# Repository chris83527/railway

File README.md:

# railway
Schematics for railway controller

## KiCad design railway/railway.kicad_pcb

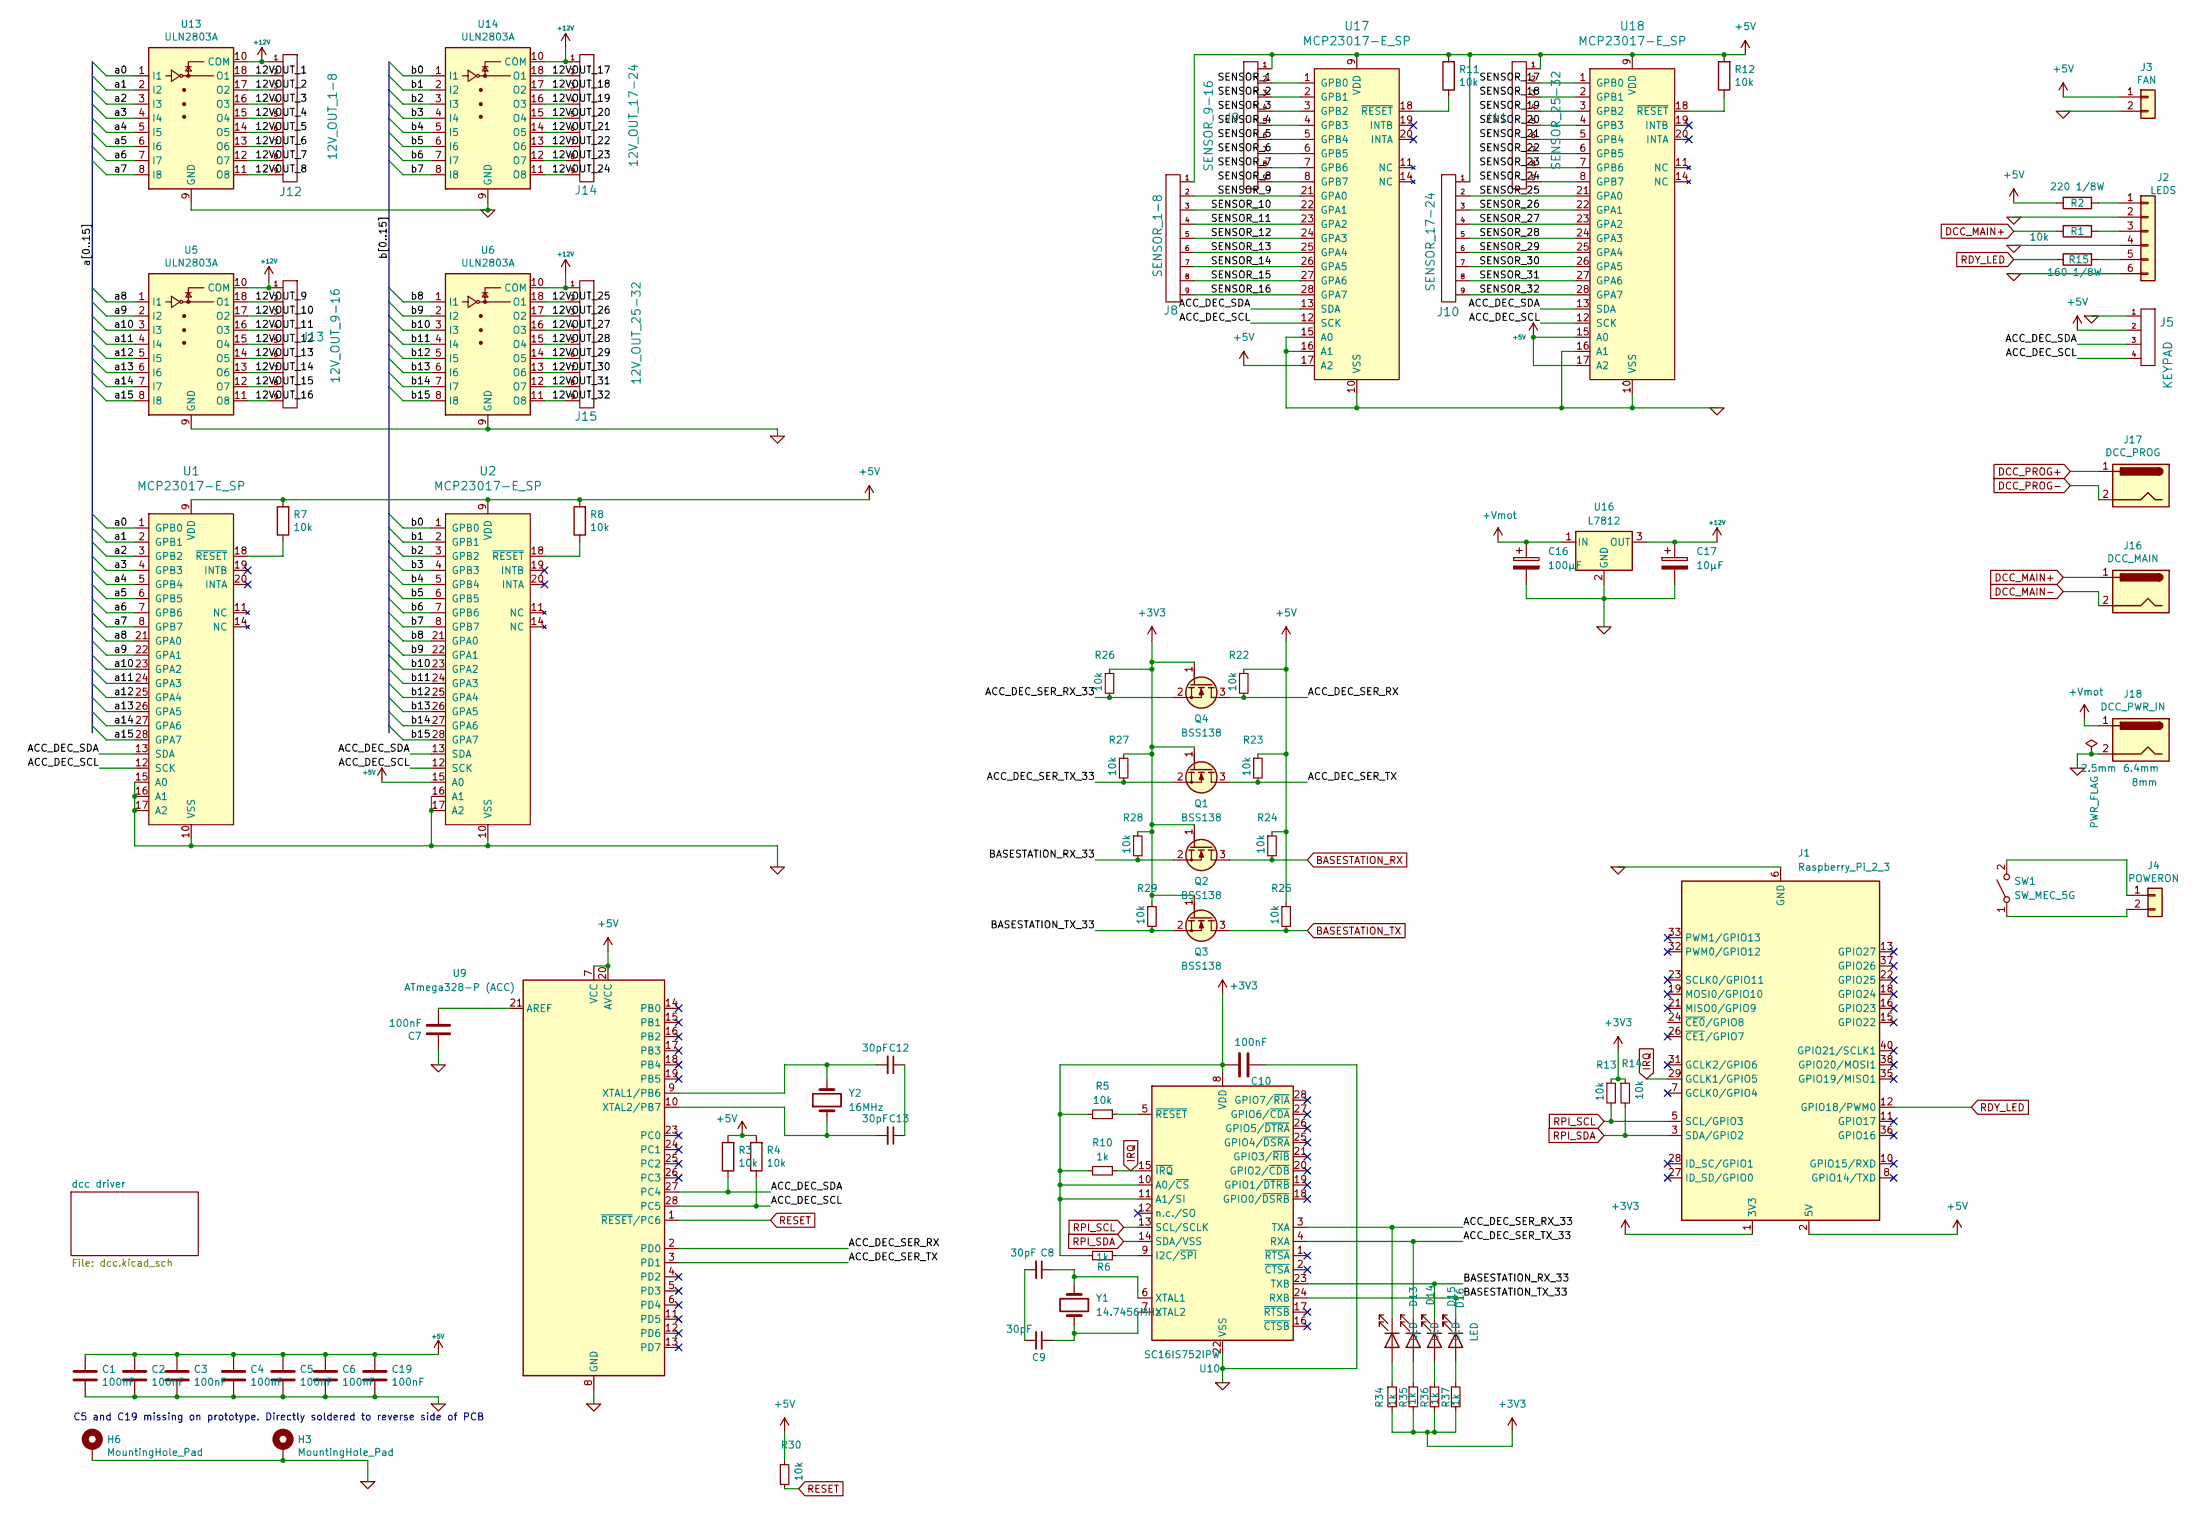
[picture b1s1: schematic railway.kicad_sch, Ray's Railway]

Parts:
C1, C2, C3, C4, C5, C6, C7, C10, C19: 100nF; C_0805_2012Metric_Pad1.18x1.45mm_HandSolder
C8, C9, C12, C13: 30pF; C_0805_2012Metric_Pad1.18x1.45mm_HandSolder
C16: 100µF; CP_Elec_4x4.5
C17: 10µF; CP_Elec_8x10.5
D13, D14, D15, D16: LED; LED_0805_2012Metric_Pad1.15x1.40mm_HandSolder
H3, H6: MountingHole_Pad; MountingHole_3.2mm_M3_Pad
J1: Raspberry_Pi_2_3; IDC-Header_2x20_P2.54mm_Vertical_reversed
J2: LEDS; JST_XH_B6B-XH-A_1x06_P2.50mm_Vertical
J3: FAN; JST_XH_B2B-XH-A_1x02_P2.50mm_Vertical
J4: POWERON; JST_XH_B2B-XH-A_1x02_P2.50mm_Vertical
J5: KEYPAD; JST_XH_B4B-XH-A_1x04_P2.50mm_Vertical
J8: SENSOR_1-8; minidin_9_pcb_mount
J9: SENSOR_9-16; minidin_9_pcb_mount
J10: SENSOR_17-24; minidin_9_pcb_mount
J11: SENSOR_25-32; minidin_9_pcb_mount
J12: 12V_OUT_1-8; minidin_9_pcb_mount
J13: 12V_OUT_9-16; minidin_9_pcb_mount
J14: 12V_OUT_17-24; minidin_9_pcb_mount
J15: 12V_OUT_25-32; minidin_9_pcb_mount
J16: DCC_MAIN; BarrelJack_Wuerth_6941xx301002
J17: DCC_PROG; BarrelJack_Wuerth_6941xx301002
J18: DCC_PWR_IN; BarrelJack_Wuerth_6941xx301002
Q1, Q2, Q3, Q4: BSS138; SOT-23
R1, R5, R7, R8, R11, R12, R13, R14, R22, R23, R24, R25, R26, R27, R28, R29, R30: 10k; R_0805_2012Metric_Pad1.20x1.40mm_HandSolder
R2: 220 1/8W; R_0805_2012Metric_Pad1.20x1.40mm_HandSolder
R3, R4: 10k; R_0805_2012Metric
R6, R10, R34, R35, R36, R37: 1k; R_0805_2012Metric_Pad1.20x1.40mm_HandSolder
R15: 160 1/8W; R_0805_2012Metric_Pad1.20x1.40mm_HandSolder
SW1: SW_MEC_5G; SW_Tactile_SKHH_Angled
U1, U2, U17, U18: MCP23017-E_SP; DIP-28_W7.62mm_Socket_LongPads; MPN MCP23017-E/SP; Digi-Key_PN MCP23017-E/SP-ND
U5, U6, U13, U14: ULN2803A; DIP-18_W7.62mm_Socket
U9: ATmega328-P (ACC); DIP-28_W7.62mm_Socket_LongPads
U10: SC16IS752IPW; TSSOP-28_4.4x9.7mm_P0.65mm
U16: L7812; TO-263-2
Y1: 14.7456MHz; Crystal_SMD_HC49-SD
Y2: 16MHz; Crystal_SMD_ECS_CSM3X-2Pin_7.6x4.1mm

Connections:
+3V3: C10.2, J1.1 (3V3), J1.17 (3V3), Q1.1 (G), Q2.1 (G), Q3.1 (G), Q4.1 (G), R5.2, R6.2, R10.2, R13.1, R14.1, R26.1, R27.1, R28.1, R29.1, R34.2, R35.2, R36.2, R37.2, U10.8 (VDD), U10.10 (A0/~CS), U10.11 (A1/SI)
+5V: C1.1, C2.1, C3.1, C4.1, C5.1, C6.1, C19.1, J1.2 (5V), J1.4 (5V), J3.1, J5.2, J8.1, J9.1, J10.1, J11.1, R2.1, R3.2, R4.2, R7.2, R8.2, R11.2, R12.2, R22.1, R23.1, R24.1, R25.1, R30.1, U1.9 (VDD), U2.9 (VDD), U2.15 (A0), U9.7 (VCC), U9.20 (AVCC), U17.9 (VDD), U17.17 (A2), U18.9 (VDD), U18.15 (A0), U18.17 (A2); also elsewhere on the board
+12V: C17.1, J12.1, J13.1, J14.1, J15.1, U5.10 (COM), U6.10 (COM), U13.10 (COM), U14.10 (COM), U16.3 (OUT)
+Vmot: C16.1, J18.1, U16.1 (IN); also elsewhere on the board
/12VOUT_1: J12.2, U13.18 (O1)
/12VOUT_2: J12.3, U13.17 (O2)
/12VOUT_3: J12.4, U13.16 (O3)
/12VOUT_4: J12.5, U13.15 (O4)
/12VOUT_5: J12.6, U13.14 (O5)
/12VOUT_6: J12.7, U13.13 (O6)
/12VOUT_7: J12.8, U13.12 (O7)
/12VOUT_8: J12.9, U13.11 (O8)
/12VOUT_9: J13.2, U5.18 (O1)
/12VOUT_10: J13.3, U5.17 (O2)
/12VOUT_11: J13.4, U5.16 (O3)
/12VOUT_12: J13.5, U5.15 (O4)
/12VOUT_13: J13.6, U5.14 (O5)
/12VOUT_14: J13.7, U5.13 (O6)
/12VOUT_15: J13.8, U5.12 (O7)
/12VOUT_16: J13.9, U5.11 (O8)
/12VOUT_17: J14.2, U14.18 (O1)
/12VOUT_18: J14.3, U14.17 (O2)
/12VOUT_19: J14.4, U14.16 (O3)
/12VOUT_20: J14.5, U14.15 (O4)
/12VOUT_21: J14.6, U14.14 (O5)
/12VOUT_22: J14.7, U14.13 (O6)
/12VOUT_23: J14.8, U14.12 (O7)
/12VOUT_24: J14.9, U14.11 (O8)
/12VOUT_25: J15.2, U6.18 (O1)
/12VOUT_26: J15.3, U6.17 (O2)
/12VOUT_27: J15.4, U6.16 (O3)
/12VOUT_28: J15.5, U6.15 (O4)
/12VOUT_29: J15.6, U6.14 (O5)
/12VOUT_30: J15.7, U6.13 (O6)
/12VOUT_31: J15.8, U6.12 (O7)
/12VOUT_32: J15.9, U6.11 (O8)
/ACC_DEC_SCL: J5.4, R4.1, U1.12 (SCK), U2.12 (SCK), U9.28 (PC5), U17.12 (SCK), U18.12 (SCK)
/ACC_DEC_SDA: J5.3, R3.1, U1.13 (SDA), U2.13 (SDA), U9.27 (PC4), U17.13 (SDA), U18.13 (SDA)
/ACC_DEC_SER_RX: Q4.3 (D), R22.2, U9.2 (PD0)
/ACC_DEC_SER_RX_33: D13.1 (K), Q4.2 (S), R26.2, U10.3 (TXA)
/ACC_DEC_SER_TX: Q1.3 (D), R23.2, U9.3 (PD1)
/ACC_DEC_SER_TX_33: D14.1 (K), Q1.2 (S), R27.2, U10.4 (RXA)
/BASESTATION_RX_33: D15.1 (K), Q2.2 (S), R28.2, U10.23 (TXB)
/BASESTATION_TX_33: D16.1 (K), Q3.2 (S), R29.2, U10.24 (RXB)
/SENSOR_1: J9.2, U17.1 (GPB0)
/SENSOR_2: J9.3, U17.2 (GPB1)
/SENSOR_3: J9.4, U17.3 (GPB2)
/SENSOR_4: J9.5, U17.4 (GPB3)
/SENSOR_5: J9.6, U17.5 (GPB4)
/SENSOR_6: J9.7, U17.6 (GPB5)
/SENSOR_7: J9.8, U17.7 (GPB6)
/SENSOR_8: J9.9, U17.8 (GPB7)
/SENSOR_9: J8.2, U17.21 (GPA0)
/SENSOR_10: J8.3, U17.22 (GPA1)
/SENSOR_11: J8.4, U17.23 (GPA2)
/SENSOR_12: J8.5, U17.24 (GPA3)
/SENSOR_13: J8.6, U17.25 (GPA4)
/SENSOR_14: J8.7, U17.26 (GPA5)
/SENSOR_15: J8.8, U17.27 (GPA6)
/SENSOR_16: J8.9, U17.28 (GPA7)
/SENSOR_17: J11.2, U18.1 (GPB0)
/SENSOR_18: J11.3, U18.2 (GPB1)
/SENSOR_19: J11.4, U18.3 (GPB2)
/SENSOR_20: J11.5, U18.4 (GPB3)
/SENSOR_21: J11.6, U18.5 (GPB4)
/SENSOR_22: J11.7, U18.6 (GPB5)
/SENSOR_23: J11.8, U18.7 (GPB6)
/SENSOR_24: J11.9, U18.8 (GPB7)
/SENSOR_25: J10.2, U18.21 (GPA0)
/SENSOR_26: J10.3, U18.22 (GPA1)
/SENSOR_27: J10.4, U18.23 (GPA2)
/SENSOR_28: J10.5, U18.24 (GPA3)
/SENSOR_29: J10.6, U18.25 (GPA4)
/SENSOR_30: J10.7, U18.26 (GPA5)
/SENSOR_31: J10.8, U18.27 (GPA6)
/SENSOR_32: J10.9, U18.28 (GPA7)
/a0: U1.1 (GPB0), U13.1 (I1)
/a1: U1.2 (GPB1), U13.2 (I2)
/a2: U1.3 (GPB2), U13.3 (I3)
/a3: U1.4 (GPB3), U13.4 (I4)
/a4: U1.5 (GPB4), U13.5 (I5)
/a5: U1.6 (GPB5), U13.6 (I6)
/a6: U1.7 (GPB6), U13.7 (I7)
/a7: U1.8 (GPB7), U13.8 (I8)
/a8: U1.21 (GPA0), U5.1 (I1)
/a9: U1.22 (GPA1), U5.2 (I2)
/a10: U1.23 (GPA2), U5.3 (I3)
/a11: U1.24 (GPA3), U5.4 (I4)
/a12: U1.25 (GPA4), U5.5 (I5)
/a13: U1.26 (GPA5), U5.6 (I6)
/a14: U1.27 (GPA6), U5.7 (I7)
/a15: U1.28 (GPA7), U5.8 (I8)
/b0: U2.1 (GPB0), U14.1 (I1)
/b1: U2.2 (GPB1), U14.2 (I2)
/b2: U2.3 (GPB2), U14.3 (I3)
/b3: U2.4 (GPB3), U14.4 (I4)
/b4: U2.5 (GPB4), U14.5 (I5)
/b5: U2.6 (GPB5), U14.6 (I6)
/b6: U2.7 (GPB6), U14.7 (I7)
/b7: U2.8 (GPB7), U14.8 (I8)
/b8: U2.21 (GPA0), U6.1 (I1)
/b9: U2.22 (GPA1), U6.2 (I2)
/b10: U2.23 (GPA2), U6.3 (I3)
/b11: U2.24 (GPA3), U6.4 (I4)
/b12: U2.25 (GPA4), U6.5 (I5)
/b13: U2.26 (GPA5), U6.6 (I6)
/b14: U2.27 (GPA6), U6.7 (I7)
/b15: U2.28 (GPA7), U6.8 (I8)
BASESTATION_RX: Q2.3 (D), R24.2; also elsewhere on the board
BASESTATION_TX: Q3.3 (D), R25.2; also elsewhere on the board
DCC_MAIN+: J16.1, R1.1; also elsewhere on the board
DCC_MAIN-: J16.2; also elsewhere on the board
DCC_PROG+: J17.1; also elsewhere on the board
DCC_PROG-: J17.2; also elsewhere on the board
GND: C1.2, C2.2, C3.2, C4.2, C5.2, C6.2, C7.1, C10.1, C16.2, C17.2, C19.2, H3.1, H6.1, J1.6 (GND), J1.9 (GND), J1.14 (GND), J1.20 (GND), J1.25 (GND), J1.30 (GND), J1.34 (GND), J1.39 (GND), J2.2, J2.4, J2.6, J3.2, J5.1, J18.2, U1.10 (VSS), U1.15 (A0), U1.16 (A1), U1.17 (A2), U2.10 (VSS), U2.16 (A1), U2.17 (A2), U5.9 (GND), U6.9 (GND), U9.8 (GND), U9.22 (GND), U10.22 (VSS), U13.9 (GND), U14.9 (GND), U16.2 (GND), U17.10 (VSS), U17.15 (A0), U17.16 (A1), U18.10 (VSS), U18.16 (A1); also elsewhere on the board
IRQ: J1.29 (GCLK1/GPIO5), R10.1, U10.15 (~IRQ)
unnamed: C8.2, C9.2
unnamed: C12.1, C13.1
unnamed: D13.2 (A), R34.1
unnamed: D14.2 (A), R35.1
unnamed: D15.2 (A), R36.1
unnamed: D16.2 (A), R37.1
unnamed: J2.1, R2.2
unnamed: J2.3, R1.2
unnamed: J2.5, R15.2
unnamed: J4.1, SW1.2 (B)
unnamed: J4.2, SW1.1 (A)
unnamed: R7.1, U1.18 (~RESET)
unnamed: R8.1, U2.18 (~RESET)
unnamed: C7.2, U9.21 (AREF)
unnamed: C12.2, U9.9 (XTAL1/PB6), Y2.2
unnamed: C13.2, U9.10 (XTAL2/PB7), Y2.1
unnamed: R6.1, U10.9 (I2C/~SPI)
unnamed: C8.1, U10.6 (XTAL1), Y1.1
unnamed: C9.1, U10.7 (XTAL2), Y1.2
unnamed: R5.1, U10.5 (~RESET)
unnamed: R11.1, U17.18 (~RESET)
unnamed: R12.1, U18.18 (~RESET)
RDY_LED: J1.12 (GPIO18/PWM0), R15.1
RESET: R30.2, U9.1 (~RESET/PC6); also elsewhere on the board
RPI_SCL: J1.5 (SCL/GPIO3), R13.2, U10.13 (SCL/SCLK)
RPI_SDA: J1.3 (SDA/GPIO2), R14.2, U10.14 (SDA/VSS)

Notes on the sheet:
C5 and C19 missing on prototype. Directly soldered to reverse side of PCB

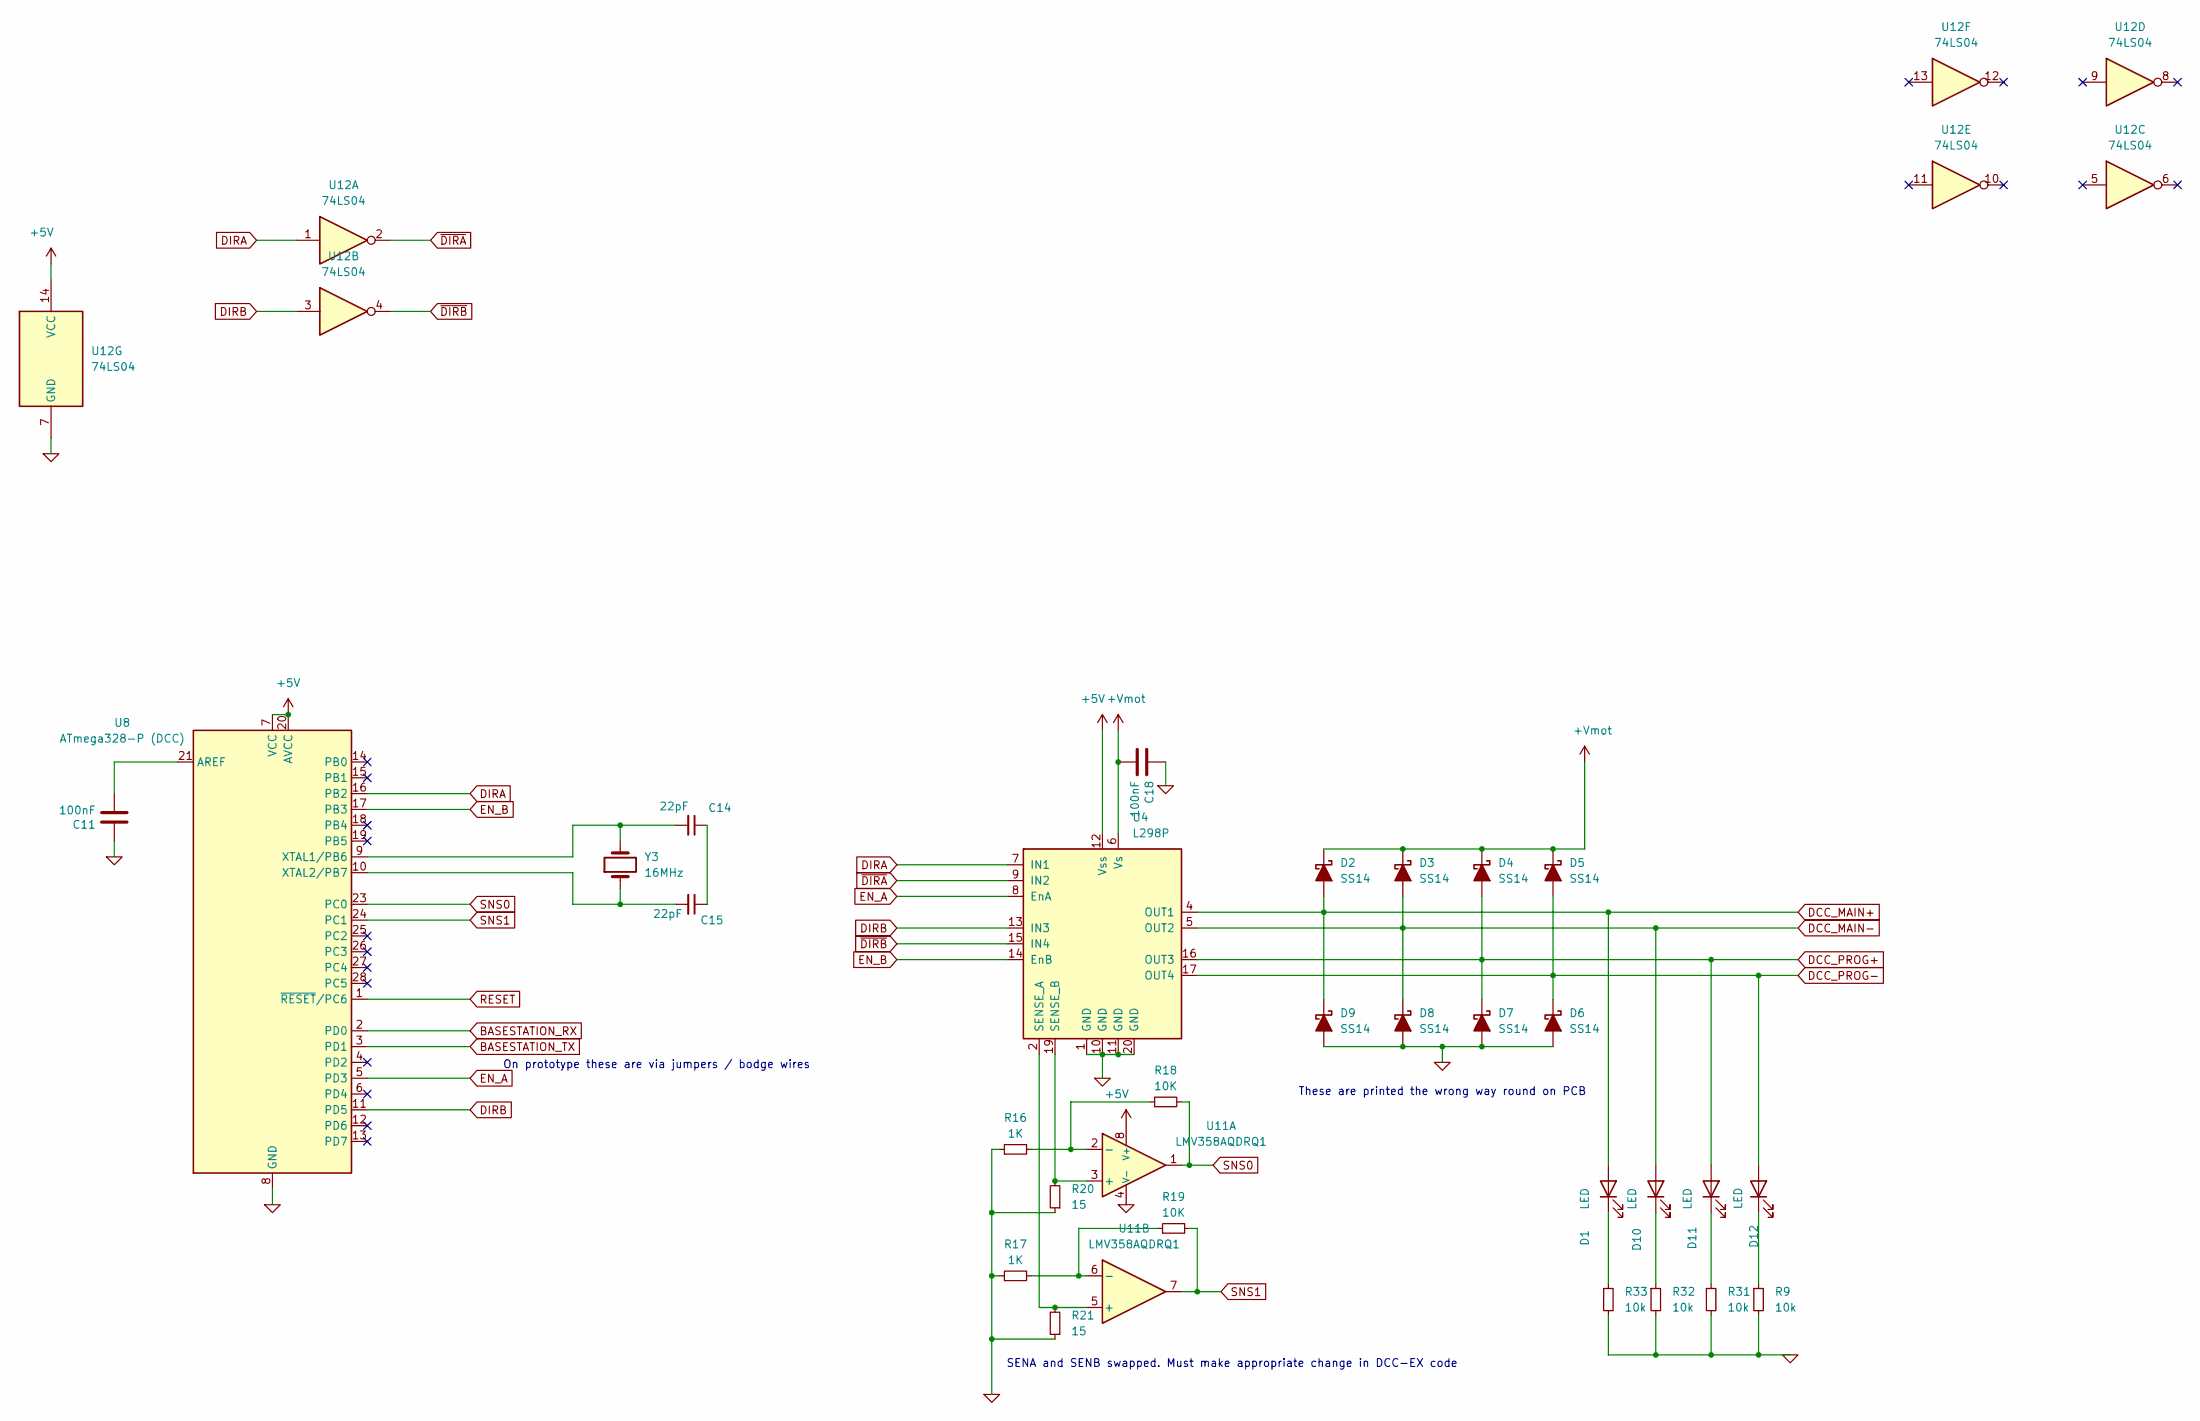
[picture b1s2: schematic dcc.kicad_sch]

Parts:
C11, C18: 100nF; C_0805_2012Metric_Pad1.18x1.45mm_HandSolder
C14, C15: 22pF; C_0805_2012Metric_Pad1.18x1.45mm_HandSolder
D1, D10, D11, D12: LED; LED_0805_2012Metric_Pad1.15x1.40mm_HandSolder
D2, D3, D4, D5, D6, D7, D8, D9: SS14; D_SMA_Handsoldering
R9, R31, R32, R33: 10k; R_0805_2012Metric_Pad1.20x1.40mm_HandSolder
R16, R17: 1K; R_0805_2012Metric_Pad1.20x1.40mm_HandSolder
R18, R19: 10K; R_0805_2012Metric_Pad1.20x1.40mm_HandSolder
R20, R21: 15; R_0805_2012Metric_Pad1.20x1.40mm_HandSolder
U4: L298P; HSOP-20-1EP_11.0x15.9mm_P1.27mm_SlugDown_ThermalVias
U8: ATmega328-P (DCC); DIP-28_W7.62mm_Socket_LongPads
U11: LMV358AQDRQ1; SSOP-8_3.9x5.05mm_P1.27mm
U12: 74LS04; SOIC-14_3.9x8.7mm_P1.27mm
Y3: 16MHz; Crystal_SMD_ECS_CSM3X-2Pin_7.6x4.1mm

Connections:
+5V: U4.12 (Vss), U8.7 (VCC), U8.20 (AVCC), U11.8 (V+), U12.14 (VCC); also elsewhere on the board
+Vmot: C18.2, D2.1 (K), D3.1 (K), D4.1 (K), D5.1 (K), U4.6 (Vs); also elsewhere on the board
BASESTATION_RX: U8.2 (PD0); also elsewhere on the board
BASESTATION_TX: U8.3 (PD1); also elsewhere on the board
DCC_MAIN+: D1.2 (A), D2.2 (A), D9.1 (K), U4.4 (OUT1); also elsewhere on the board
DCC_MAIN-: D3.2 (A), D8.1 (K), D10.2 (A), U4.5 (OUT2); also elsewhere on the board
DCC_PROG+: D4.2 (A), D7.1 (K), D11.2 (A), U4.16 (OUT3); also elsewhere on the board
DCC_PROG-: D5.2 (A), D6.1 (K), D12.2 (A), U4.17 (OUT4); also elsewhere on the board
DIRA: U4.7 (IN1), U8.16 (PB2), U12.1
DIRB: U4.13 (IN3), U8.11 (PD5), U12.3
EN_A: U4.8 (EnA), U8.5 (PD3)
EN_B: U4.14 (EnB), U8.17 (PB3)
GND: C11.1, C18.1, D6.2 (A), D7.2 (A), D8.2 (A), D9.2 (A), R9.2, R16.1, R17.1, R20.1, R21.1, R31.2, R32.2, R33.2, U4.1 (GND), U4.10 (GND), U4.11 (GND), U4.20 (GND), U8.8 (GND), U8.22 (GND), U11.4 (V-), U12.7 (GND); also elsewhere on the board
unnamed: C14.1, C15.1
unnamed: D1.1 (K), R33.1
unnamed: D10.1 (K), R32.1
unnamed: D11.1 (K), R31.1
unnamed: D12.1 (K), R9.1
unnamed: C11.2, U8.21 (AREF)
unnamed: C14.2, U8.9 (XTAL1/PB6), Y3.2
unnamed: C15.2, U8.10 (XTAL2/PB7), Y3.1
unnamed: R20.2, U4.19 (SENSE_B), U11.3 (+)
unnamed: R16.2, R18.1, U11.2 (-)
unnamed: R21.2, U4.2 (SENSE_A), U11.5 (+)
unnamed: R17.2, R19.1, U11.6 (-)
RESET: U8.1 (~RESET/PC6); also elsewhere on the board
SNS0: R18.2, U8.23 (PC0), U11.1
SNS1: R19.2, U8.24 (PC1), U11.7
~DIRA: U4.9 (IN2), U12.2
~DIRB: U4.15 (IN4), U12.4

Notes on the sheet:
On prototype these are via jumpers / bodge wires
SENA and SENB swapped. Must make appropriate change in DCC-EX code
These are printed the wrong way round on PCB

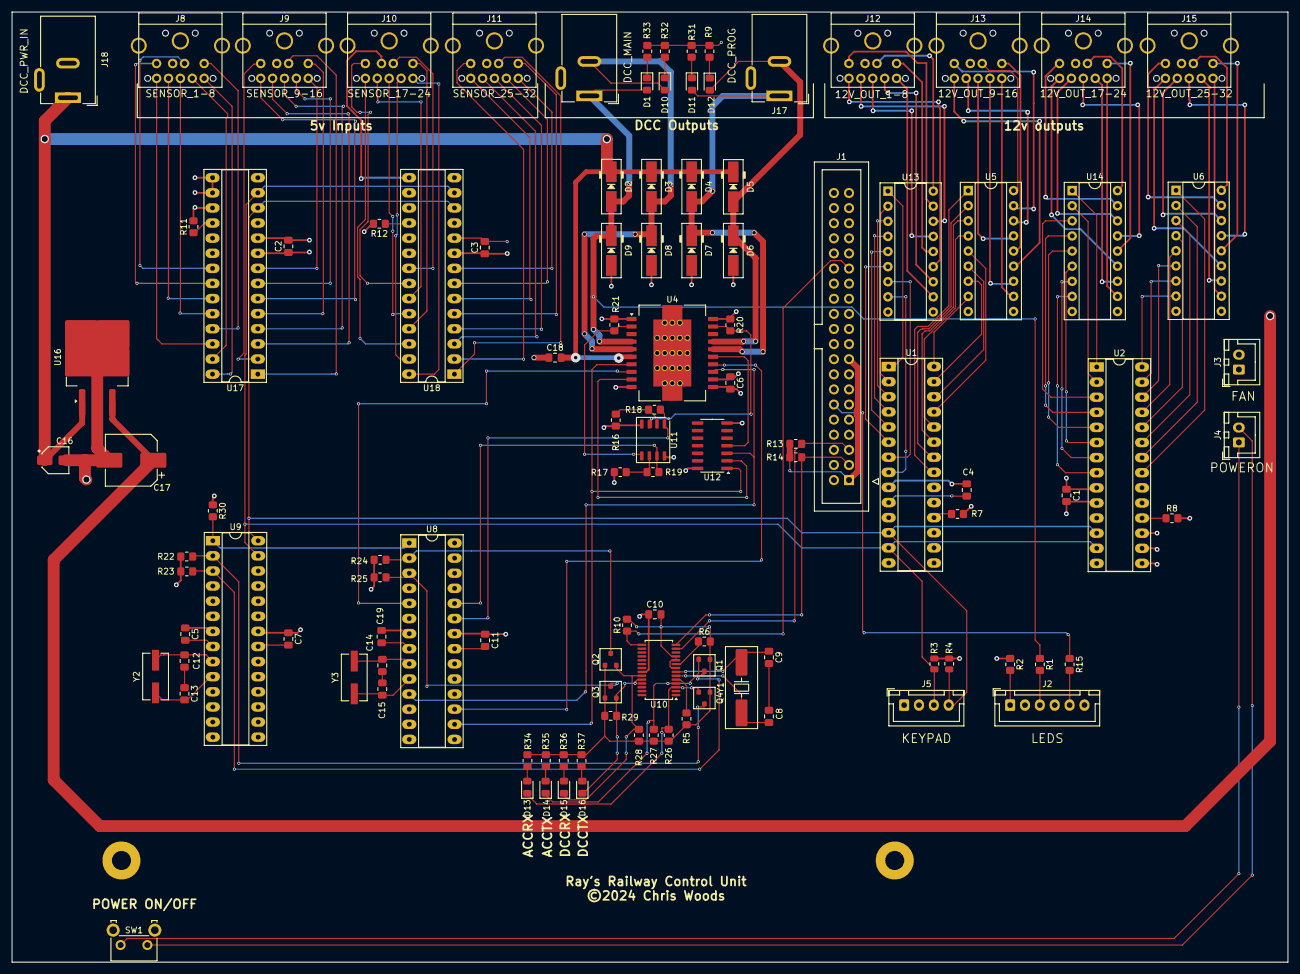
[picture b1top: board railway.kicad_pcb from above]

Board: 4 copper layers, 214.5 x 159.7 mm, 113 parts (0 on the bottom side), 162 nets.

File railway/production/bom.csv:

Designator,Footprint,Quantity,Value,LCSC Part #
"C1, C10, C11, C18, C2, C3, C4, C6, C7",0805,9,100nF,
"C12, C13, C8, C9",0805,4,30pF,
"C14, C15",0805,2,22pF,
C16,CP_Elec_4x4.5,1,100µF,
C17,CP_Elec_8x10.5,1,10µF,
"D1, D10, D11, D12, D13, D14, D15, D16",0805,8,LED,
"D2, D3, D4, D5, D6, D7, D8, D9",D_SMA_Handsoldering,8,SS14,
"H3, H6",MountingHole_3.2mm_M3_Pad,2,MountingHole_Pad,
J1,IDC-Header_2x20_P2.54mm_Vertical_reversed,1,Raspberry_Pi_2_3,
J10,minidin_9_pcb_mount,1,SENSOR_17-24,
J11,minidin_9_pcb_mount,1,SENSOR_25-32,
J12,minidin_9_pcb_mount,1,12V_OUT_1-8,
J13,minidin_9_pcb_mount,1,12V_OUT_9-16,
J14,minidin_9_pcb_mount,1,12V_OUT_17-24,
J15,minidin_9_pcb_mount,1,12V_OUT_25-32,
J16,BarrelJack_Wuerth_6941xx301002,1,DCC_MAIN,
J17,BarrelJack_Wuerth_6941xx301002,1,DCC_PROG,
J18,BarrelJack_Wuerth_6941xx301002,1,DCC_PWR_IN,
"J19, J20, J6, J7",Jumper_P2.54mm_D0.7mm,4,TX,
J2,JST_XH_B6B-XH-A_1x06_P2.50mm_Vertical,1,LEDS,
J3,JST_XH_B2B-XH-A_1x02_P2.50mm_Vertical,1,FAN,
J4,JST_XH_B2B-XH-A_1x02_P2.50mm_Vertical,1,POWERON,
J5,JST_XH_B4B-XH-A_1x04_P2.50mm_Vertical,1,KEYPAD,
J8,minidin_9_pcb_mount,1,SENSOR_1-8,
J9,minidin_9_pcb_mount,1,SENSOR_9-16,
"Q1, Q2, Q3, Q4",SOT-23,4,BSS138,
"R1, R11, R12, R13, R14, R18, R19, R22, R23, R24, R25, R26, R27, R28, R29, R3, R30, R31, R32, R33, R4, R5, R7, R8, R9",0805,25,10k,
"R10, R16, R17, R6",0805,4,1k,
R15,0805,1,160 1/8W,
R2,0805,1,220 1/8W,
"R20, R21",0805,2,15,
"R34, R35, R36, R37",0805,4,75,
SW1,SW_Tactile_SKHH_Angled,1,SW_MEC_5G,
"U1, U17, U18, U2",DIP-28_W7.62mm_Socket_LongPads,4,MCP23017-E_SP,MCP23017-E/SP
U10,TSSOP-28_4.4x9.7mm_P0.65mm,1,SC16IS752IPW,
U11,MSOP-8_3x3mm_P0.65mm,1,LMV358AQDRQ1,
U12,SOIC-14_3.9x8.7mm_P1.27mm,1,74LS04,
"U13, U14, U5, U6",DIP-18_W7.62mm_Socket,4,ULN2803A,
U16,TO-263-2,1,L7812,
U4,HSOP-20-1EP_11.0x15.9mm_P1.27mm_SlugDown_ThermalVias,1,L298P,
U8,DIP-28_W7.62mm_Socket_LongPads,1,ATmega328-P (DCC),
U9,DIP-28_W7.62mm_Socket_LongPads,1,ATmega328-P (ACC),
Y1,Crystal_SMD_HC49-SD,1,14.7456MHz,
"Y2, Y3",Crystal_SMD_ECS_CSM3X-2Pin_7.6x4.1mm,2,16MHz,

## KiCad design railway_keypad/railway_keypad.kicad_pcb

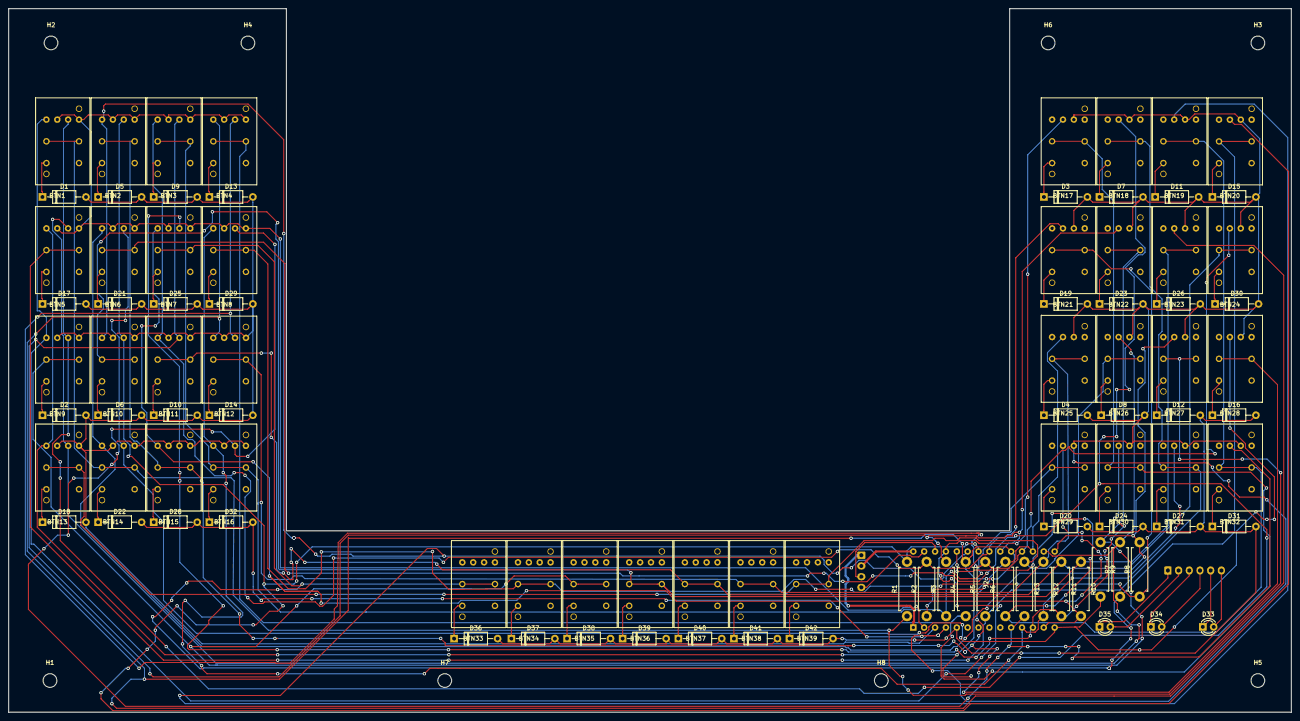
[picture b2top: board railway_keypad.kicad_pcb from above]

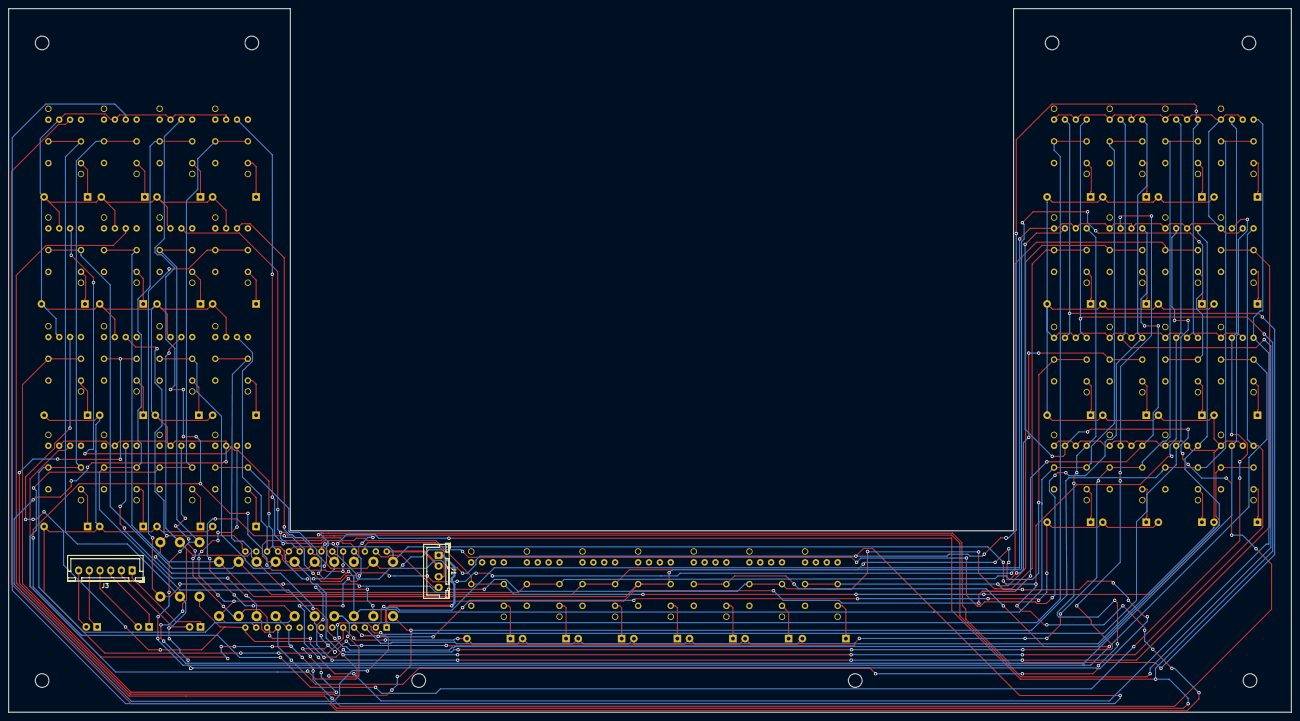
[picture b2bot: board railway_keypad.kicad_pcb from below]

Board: 2 copper layers, 299.7 x 164.4 mm, 105 parts (2 on the bottom side), 82 nets.

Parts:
BTN1, BTN2, BTN3, BTN4, BTN5, BTN6, BTN7, BTN8, BTN9, BTN10, BTN11, BTN12, BTN13, BTN14, BTN15, BTN16: PB86-A2; PB86
BTN17, BTN18, BTN19, BTN20, BTN21, BTN22, BTN23, BTN24, BTN25, BTN26, BTN27, BTN28, BTN29, BTN30, BTN31, BTN32, BTN33, BTN34, BTN35, BTN36, BTN37, BTN38, BTN39: PB86-A1; PB86
D1, D2, D3, D4, D5, D6, D7, D8, D9, D10, D11, D12, D13, D14, D15, D16, D17, D18, D19, D20, D21, D22, D23, D24, D25, D26, D27, D28, D29, D30, D31, D32, D36, D37, D38, D39, D40, D41, D42: D; D_A-405_P10.16mm_Horizontal
D33, D34, D35: LED; LED_D3.0mm
H1, H2, H3, H4, H5, H6, H7, H8: MountingHole; MountingHole_3.2mm_M3
J1: HEADER_4; JST_XH_B4B-XH-A_1x04_P2.50mm_Vertical
J2: HT16K33; DIP-28_W20,32mm
J3: HEADER_6; JST_XH_B6B-XH-A_1x06_P2.50mm_Vertical
R1, R2, R3, R4, R5, R6, R7, R8, R9, R10, R11, R12, R13: 39k; R_Axial_DIN0411_L9.9mm_D3.6mm_P12.70mm_Horizontal

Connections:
/COM0: BTN1.5, BTN1.7, BTN2.5, BTN2.7, BTN3.5, BTN3.7, BTN4.5, BTN4.7, BTN5.5, BTN5.7, BTN6.5, BTN6.7, BTN7.5, BTN7.7, BTN8.5, BTN8.7, J2.2
/COM1: BTN9.5, BTN9.7, BTN10.5, BTN10.7, BTN11.5, BTN11.7, BTN12.5, BTN12.7, BTN13.5, BTN13.7, BTN14.5, BTN14.7, BTN15.5, BTN15.7, BTN16.5, BTN16.7, D1.2, D2.2, D5.2, D6.2, D9.2, D10.2, D13.2, D14.2, D17.2, D18.2, D21.2, D25.2, D29.2, J2.3
/COM2: BTN17.6, BTN18.6, BTN19.6, BTN20.6, BTN21.6, BTN22.6, BTN23.6, BTN24.6, BTN25.6, BTN26.6, BTN27.6, BTN28.6, BTN29.6, BTN30.6, BTN31.6, BTN32.6, D3.2, D4.2, D7.2, D8.2, D11.2, D15.2, D19.2, D22.2, D23.2, D26.2, D28.2, D30.2, D32.2, J2.4
/COM3: D12.2, D16.2, D20.2, D24.2, D27.2, D31.2, D36.2, D37.2, D38.2, D39.2, D40.2, D41.2, D42.2, J2.5
/I2C_SCL: J1.3, J2.26
/I2C_SDA: J1.4, J2.27
/ROW0: BTN1.4, BTN9.4, BTN17.5, J2.25
/ROW1: BTN1.6, BTN9.6, BTN18.5, J2.24
/ROW2: BTN2.4, BTN10.4, BTN19.5, J2.23
/ROW3: BTN2.6, BTN10.6, BTN20.5, J2.22, R1.2
/ROW3_BTN: BTN1.1, BTN14.1, BTN27.1, R1.1
/ROW4: BTN3.4, BTN11.4, BTN21.5, J2.21, R2.2
/ROW4_BTN: BTN2.1, BTN15.1, BTN28.1, R2.1
/ROW5: BTN3.6, BTN11.6, BTN22.5, J2.20, R3.2
/ROW5_BTN: BTN3.1, BTN16.1, BTN29.1, R3.1
/ROW6: BTN4.4, BTN12.4, BTN23.5, J2.19, R4.2
/ROW6_BTN: BTN4.1, BTN17.1, BTN30.1, R4.1
/ROW7: BTN4.6, BTN12.6, BTN24.5, J2.18, R5.2
/ROW7_BTN: BTN5.1, BTN18.1, BTN31.1, R5.1
/ROW8: BTN5.4, BTN13.4, BTN25.5, J2.17, R6.2
/ROW8_BTN: BTN6.1, BTN19.1, BTN32.1, R6.1
/ROW9: BTN5.6, BTN13.6, BTN26.5, J2.16, R7.2
/ROW9_BTN: BTN7.1, BTN20.1, BTN33.1, R7.1
/ROW10: BTN6.4, BTN14.4, BTN27.5, J2.15, R8.2
/ROW10_BTN: BTN8.1, BTN21.1, BTN34.1, R8.1
/ROW11: BTN6.6, BTN14.6, BTN28.5, J2.14, R9.2
/ROW11_BTN: BTN9.1, BTN22.1, BTN35.1, R9.1
/ROW12: BTN7.4, BTN15.4, BTN29.5, J2.13, R10.2
/ROW12_BTN: BTN10.1, BTN23.1, BTN36.1, R10.1
/ROW13: BTN7.6, BTN15.6, BTN30.5, J2.12, R11.2
/ROW13_BTN: BTN11.1, BTN24.1, BTN37.1, R11.1
/ROW14: BTN8.4, BTN16.4, BTN31.5, J2.11, R12.2
/ROW14_BTN: BTN12.1, BTN25.1, BTN38.1, R12.1
/ROW15: BTN8.6, BTN16.6, BTN32.5, J2.10, R13.2
/ROW15_BTN: BTN13.1, BTN26.1, BTN39.1, R13.1
GND: J1.1, J2.1
unnamed: BTN1.2, D1.1
unnamed: BTN2.2, D5.1
unnamed: BTN3.2, D9.1
unnamed: BTN4.2, D13.1
unnamed: BTN5.2, D17.1
unnamed: BTN6.2, D21.1
unnamed: BTN7.2, D25.1
unnamed: BTN8.2, D29.1
unnamed: BTN9.2, D2.1
unnamed: BTN10.2, D6.1
unnamed: BTN11.2, D10.1
unnamed: BTN12.2, D14.1
unnamed: BTN13.2, D18.1
unnamed: BTN14.2, D22.1
unnamed: BTN15.2, D28.1
unnamed: BTN16.2, D32.1
unnamed: BTN17.2, D3.1
unnamed: BTN18.2, D7.1
unnamed: BTN19.2, D11.1
unnamed: BTN20.2, D15.1
unnamed: BTN21.2, D19.1
unnamed: BTN22.2, D23.1
unnamed: BTN23.2, D26.1
unnamed: BTN24.2, D30.1
unnamed: BTN25.2, D4.1
unnamed: BTN26.2, D8.1
unnamed: BTN27.2, D12.1
unnamed: BTN28.2, D16.1
unnamed: BTN29.2, D20.1
unnamed: BTN30.2, D24.1
unnamed: BTN31.2, D27.1
unnamed: BTN32.2, D31.1
unnamed: BTN33.2, D36.1
unnamed: BTN34.2, D37.1
unnamed: BTN35.2, D38.1
unnamed: BTN36.2, D39.1
unnamed: BTN37.2, D40.1
unnamed: BTN38.2, D41.1
unnamed: BTN39.2, D42.1
unnamed: D33.1, J3.5
unnamed: D33.2, J3.6
unnamed: D34.1, J3.3
unnamed: D34.2, J3.4
unnamed: D35.1, J3.1
unnamed: D35.2, J3.2
VCC: J1.2, J2.28

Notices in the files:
railway/railway.kicad_pcb:
©2024 Chris Woods
